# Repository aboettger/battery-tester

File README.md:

# Primary cell tester (battery tester)

AA and AAA cells

## Rev 2 (WIP)

## Rev 1

**!!!Capacitor is reversed!!!**

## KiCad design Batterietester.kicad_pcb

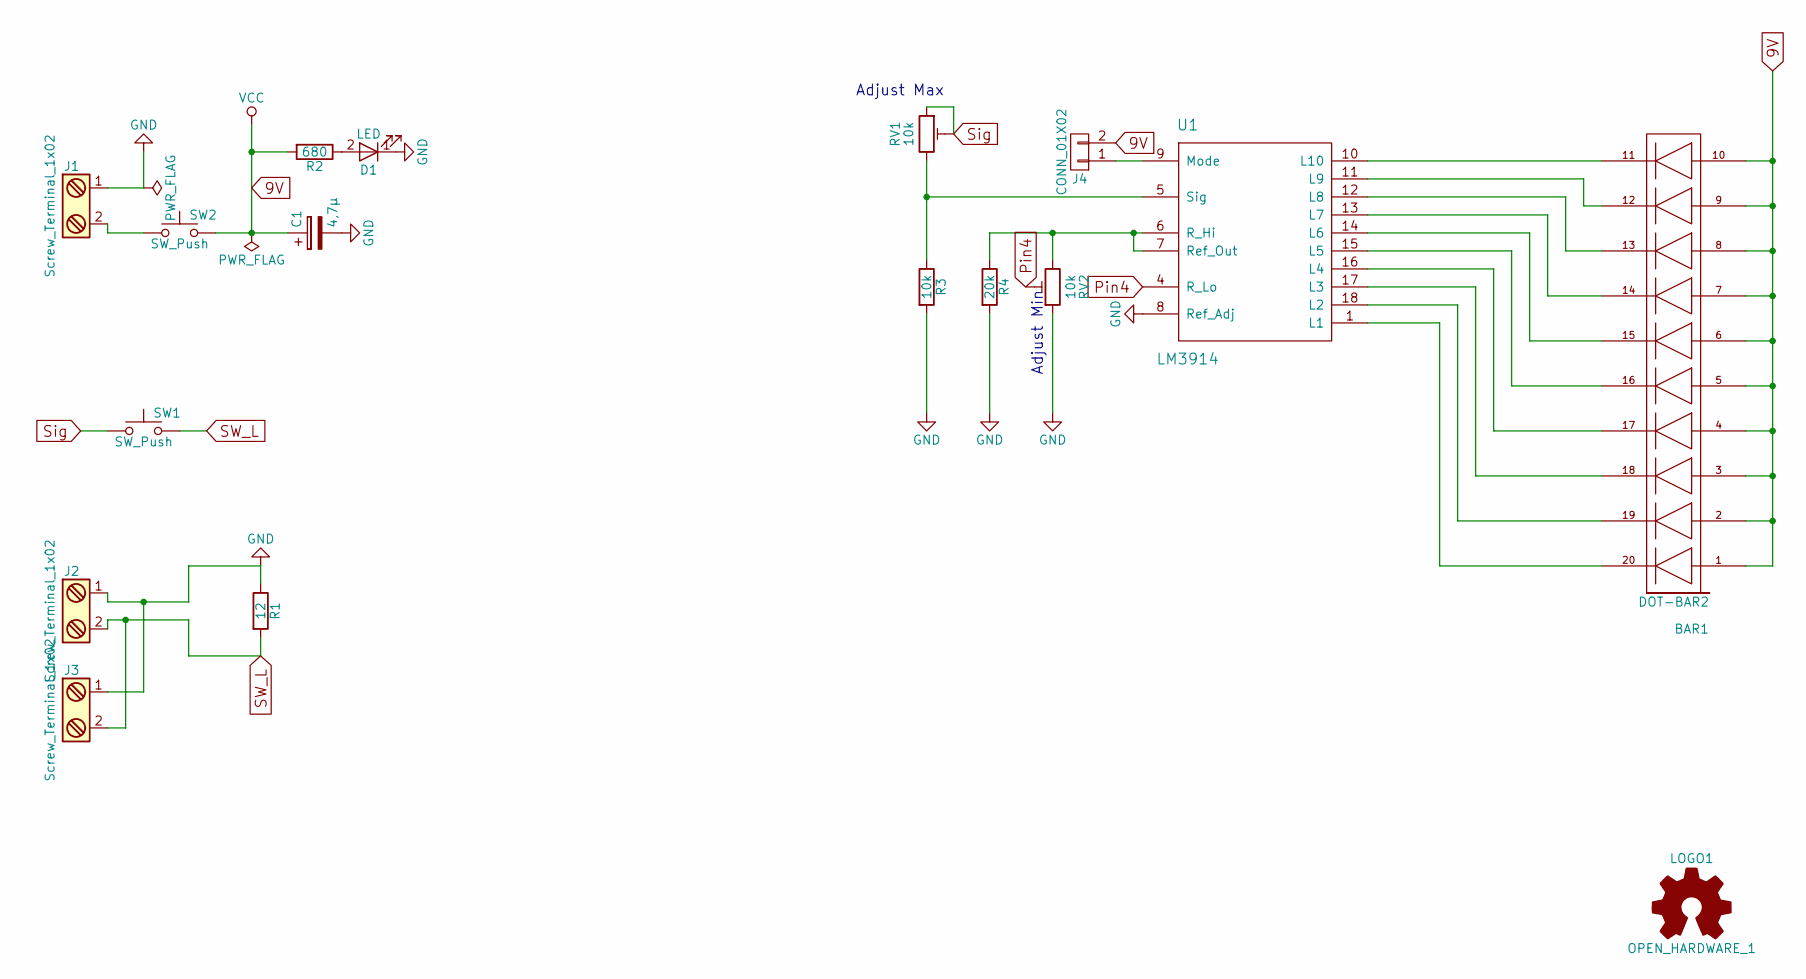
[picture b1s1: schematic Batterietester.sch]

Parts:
BAR1: DOT-BAR2; DIP-20_W7.62mm_Socket
C1: 4,7µ; CP_Radial_D4.0mm_P1.50mm
D1: LED; LED_D3.0mm
J1, J2, J3: Screw_Terminal_1x02; TerminalBlock_Phoenix_MKDS1.5-2pol
J4: CONN_01X02; Pin_Header_Straight_1x02_Pitch2.54mm
LOGO1: OPEN_HARDWARE_1; OSHW-Logo2_9.8x8mm_SilkScreen
R1: 12; R_Axial_DIN0207_L6.3mm_D2.5mm_P10.16mm_Horizontal
R2: 680; R_Axial_DIN0207_L6.3mm_D2.5mm_P10.16mm_Horizontal
R3: 10k; R_Axial_DIN0207_L6.3mm_D2.5mm_P10.16mm_Horizontal
R4: 20k; R_Axial_DIN0207_L6.3mm_D2.5mm_P10.16mm_Horizontal
RV1, RV2: 10k; Potentiometer_Trimmer_Copal_CT-6EP
SW1, SW2: SW_Push; SW_PUSH_6mm
U1: LM3914; DIP-18_W7.62mm_Socket

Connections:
9V: BAR1.1 (A), BAR1.2 (A), BAR1.3 (A), BAR1.4 (A), BAR1.5 (A), BAR1.6 (A), BAR1.7 (A), BAR1.8 (A), BAR1.9 (A), BAR1.10 (A), C1.1, J4.2, R2.2, SW2.2, U1.3 (Vcc)
GND: C1.2, D1.1 (K), J1.1, J2.1, J3.1, R1.1, R3.2, R4.2, RV2.1, U1.2 (Gnd), U1.8 (Ref_Adj)
unnamed: BAR1.11 (K), U1.10 (L10)
unnamed: BAR1.12 (K), U1.11 (L9)
unnamed: BAR1.13 (K), U1.12 (L8)
unnamed: BAR1.14 (K), U1.13 (L7)
unnamed: BAR1.15 (K), U1.14 (L6)
unnamed: BAR1.16 (K), U1.15 (L5)
unnamed: BAR1.17 (K), U1.16 (L4)
unnamed: BAR1.18 (K), U1.17 (L3)
unnamed: BAR1.19 (K), U1.18 (L2)
unnamed: BAR1.20 (K), U1.1 (L1)
unnamed: D1.2 (A), R2.1
unnamed: J1.2, SW2.1
unnamed: J4.1, U1.9 (Mode)
unnamed: R3.1, RV1.3, U1.5 (Sig)
unnamed: R4.1, RV2.3, U1.6 (R_Hi), U1.7 (Ref_Out)
Pin4: RV2.2, U1.4 (R_Lo)
SW_L: J2.2, J3.2, R1.2, SW1.2
Sig: RV1.1, RV1.2, SW1.1

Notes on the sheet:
Adjust Min
Adjust Max

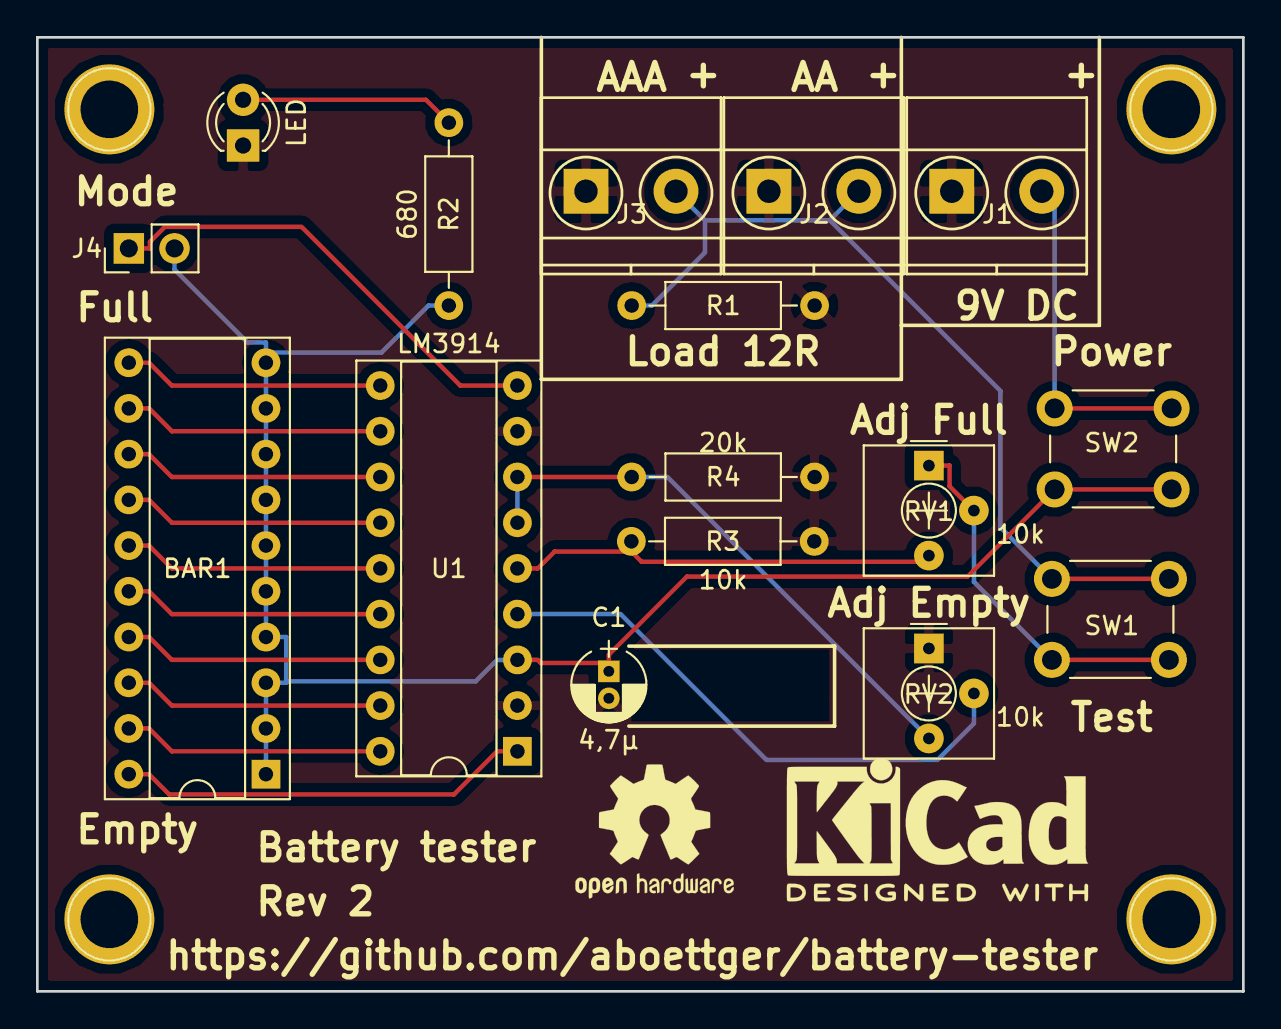
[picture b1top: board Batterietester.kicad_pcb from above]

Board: 2 copper layers, 67.0 x 53.0 mm, 22 parts (0 on the bottom side), 20 nets.

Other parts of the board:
H1, H2, H3, H4: 1pin
kicad: KiCad-Logo2_8mm_SilkScreen

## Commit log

2017-11-10 Update LICENSE
2017-11-10 initial
2017-11-10 ignore .directory files
2017-11-10 ignore _saved_*
2017-11-10 Board design
2017-11-10 Preview image
2017-11-10 added Filled zones
2017-11-10 foobar
2017-11-10 new image
2017-11-10 fixed typo
2017-11-10 corrected orientation
2017-11-11 added mounting holes added mode jumper
2017-11-13 corrected LED bar connection
2017-11-13 changed variable resistors
2017-11-13 added revision
2017-11-13 finished Rev 1
2017-11-13 changed preview image
2017-11-30 layout changes
2017-11-30 Images
2017-12-01 change layout
2017-12-01 redesign
    - add terminal blocks
    - use freerouter
    - fix some ref errors
2017-12-01 clean files
2017-12-01 swap positions RV1, RV2
2017-12-01 wording
2017-12-01 cleaning
2017-12-01 rev 2 wip images
2017-12-01 correct capacitor
2017-12-01 use polarized capacitor
2017-12-02 change open hardware
